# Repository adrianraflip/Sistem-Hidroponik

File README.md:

# Sistem-Hidroponik
Project Sistem Hidroponik

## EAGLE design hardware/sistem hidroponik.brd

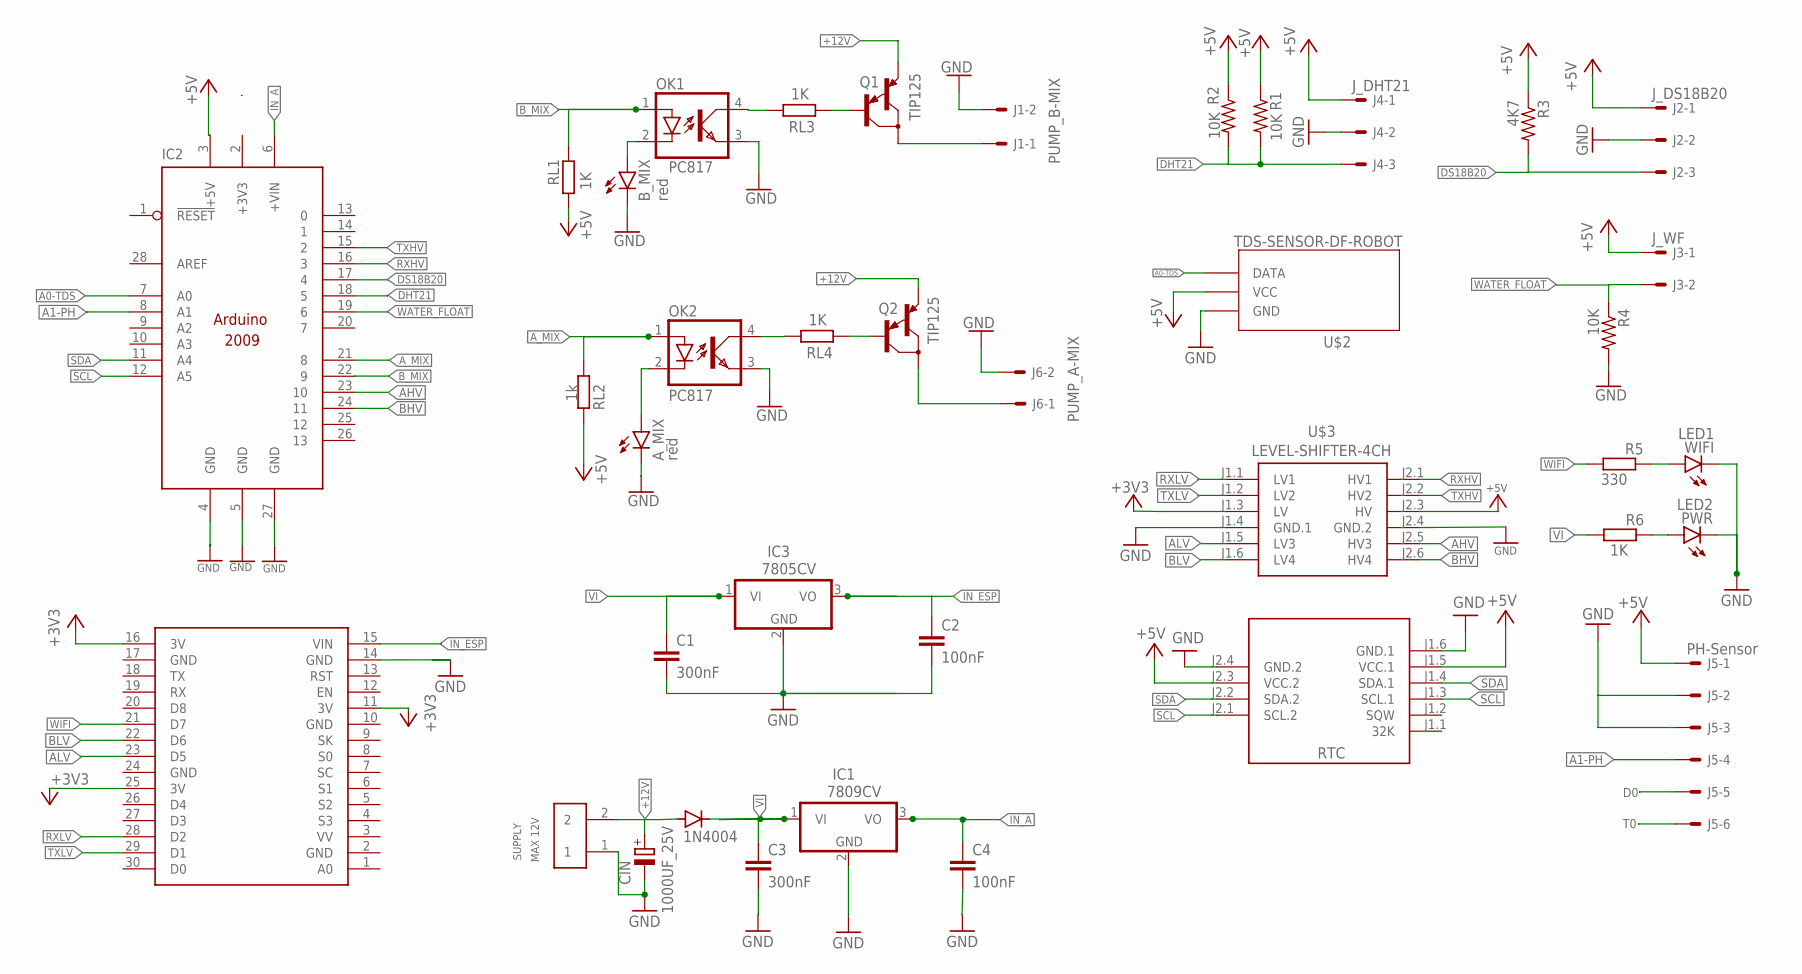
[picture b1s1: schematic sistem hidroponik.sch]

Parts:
1K: R6; 0207/7
330: R5; 0207/7
A_MIX: red; LED3MM
B_MIX: red; LED3MM
C1, C3: 300nF; C025-030X050
C2, C4: 100nF; C025-030X050
CIN: 1000UF_25V; E3,5-8
D1: 1N4004; DO41-10
IC1: 7809CV; TO220H
IC2: ARDUINO2009_10; ARDUINO2009
IC3: 7805CV; TO220H
J1: PUMP_B-MIX; 6410-02
J2: J_DS18B20; 6410-03
J3: J_WF; 6410-02
J4: J_DHT21; 6410-03
J5: PH-Sensor; 6410-06
J6: PUMP_A-MIX; 6410-02
OK1, OK2: PC817; DIL04
PWR: LED2; LED3MM
Q1, Q2: TIP125; TO220
R1, R2, R4: 10K; 0204/7
R3: 4K7; 0204/7
RL1, RL3, RL4: 1K; 0207/7
RL2: 1k; 0207/7
RTC: RTC-DS3231-AT24C32
SUPPLY: MAX 12V; OST_TBLOCK-2PIN
U$1: NODEMCU
U$2: TDS-SENSOR-DF-ROBOT; TDS-SENSOR
U$3: LEVEL-SHIFTER-4CH
WIFI: LED1; LED3MM

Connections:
+3V3: IC2.2 (+3V3), U$1.11 (3V), U$1.16 (3V), U$1.25 (3V), U$3.J1.3 (LV)
+5V: IC2.3 (+5V), J2.1, J3.1, J4.1, J5.1, R1.1, R2.1, R3.1, RL1.1, RL2.2, RTC.J1.5 (VCC.1), RTC.J2.3 (VCC.2), U$2.VCC, U$3.J2.3 (HV)
+12V: CIN.+, D1.A, Q1.3 (E), Q2.3 (E), SUPPLY.2
A0-TDS: IC2.7 (A0), U$2.A (DATA)
A1-PH: IC2.8 (A1), J5.4
AHV: IC2.23 (10), U$3.J2.5 (HV3)
ALV: U$1.23 (D5), U$3.J1.5 (LV3)
A_MIX: IC2.21 (8), OK2.1 (A), RL2.1
BHV: IC2.24 (11), U$3.J2.6 (HV4)
BLV: U$1.22 (D6), U$3.J1.6 (LV4)
B_MIX: IC2.22 (9), OK1.1 (A), RL1.2
D0: J5.5
DHT21: IC2.18 (5), J4.3, R1.2, R2.2
DS18B20: IC2.17 (4), J2.3, R3.2
GND: A_MIX.K (C), B_MIX.K (C), C1.2, C2.2, C3.2, C4.2, CIN.-, IC1.2 (GND), IC2.4 (GND), IC2.5 (GND), IC2.27 (GND), IC3.2 (GND), J1.2, J2.2, J4.2, J5.2, J5.3, J6.2, OK1.3 (EMIT), OK2.3 (EMIT), PWR.K (C), R4.2, RTC.J1.6 (GND.1), RTC.J2.4 (GND.2), SUPPLY.1, U$1.2 (GND), U$1.10 (GND), U$1.14 (GND), U$1.17 (GND), U$1.24 (GND), U$2.GND, U$3.J1.4 (GND.1), U$3.J2.4 (GND.2), WIFI.K (C)
IN_A: C4.1, IC1.3 (VO), IC2.6 (+VIN)
IN_ESP: C2.1, IC3.3 (VO), U$1.15 (VIN)
unnamed: J1.1, Q1.2 (C)
unnamed: 330.1, WIFI.A
unnamed: J6.1, Q2.2 (C)
unnamed: 1K.1, PWR.A
unnamed: B_MIX.A, OK1.2 (C)
unnamed: A_MIX.A, OK2.2 (C)
unnamed: OK2.4 (COL), RL4.2
unnamed: Q2.1 (B), RL4.1
unnamed: Q1.1 (B), RL3.1
unnamed: OK1.4 (COL), RL3.2
RXHV: IC2.16 (3), U$3.J2.1 (HV1)
RXLV: U$1.28 (D2), U$3.J1.1 (LV1)
SCL: IC2.12 (A5), RTC.J1.3 (SCL.1), RTC.J2.1 (SCL.2)
SDA: IC2.11 (A4), RTC.J1.4 (SDA.1), RTC.J2.2 (SDA.2)
T0: J5.6
TXHV: IC2.15 (2), U$3.J2.2 (HV2)
TXLV: U$1.29 (D1), U$3.J1.2 (LV2)
VI: 1K.2, C1.1, C3.1, D1.C, IC1.1 (VI), IC3.1 (VI)
WATER_FLOAT: IC2.19 (6), J3.2, R4.1
WIFI: 330.2, U$1.21 (D7)

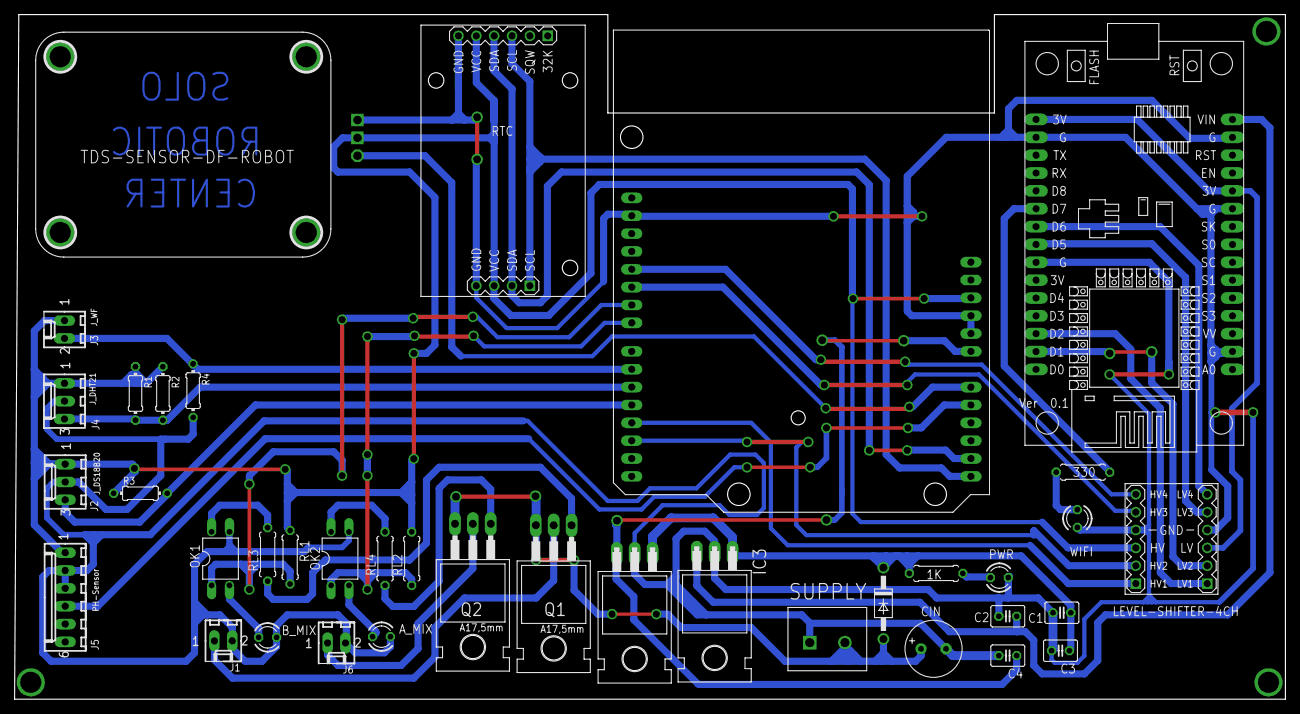
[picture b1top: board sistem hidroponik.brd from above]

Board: 2 copper layers, 180.8 x 97.4 mm, 38 parts (1 on the bottom side), 35 nets.

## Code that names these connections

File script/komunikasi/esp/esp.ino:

/*
ARDUINO UNO 
------------------------
MOTOR A MIX = 8  => LED 
MOTOR B MIX = 9  => LED
WATER FLOAT = 6
DHT 21 = 5
DS18b20 = 4 
TX = 3
TX = 2
AHV = 10
BHV = 11
A0 = TDS SENSOR
A1 = PH SENSOR
A4 = SDA
A5 = SCL 

-----------------------------
ESP8266 
-------------------------------
LED WIFI = D7 GPIO13
BLV = D6
ALV = D5
RXLV = D2 / 4
TXLV = D1 /5
---------------------------------------
led power (1  MERAH)
led wifi (1 hijau)
led ab mix ( 2 kuning )
----------------------------------
D8/gpio15
D4/gpio2
D3/ gpio0
D0/ gpio16
d5 / 14
d6/12
d7/13

---------------------------------------------
ALTERNATIF  PROGRAM KOMUNIKASI BERHASIL
--------------------------------------------
UNO | ESP
2       |  RX
3       | TX

*/


#include <SoftwareSerial.h>
#include <BlynkSimpleEsp8266.h>
#include <ESP8266WiFi.h>
#define BLYNK_PRINT Serial
BlynkTimer timer;
SoftwareSerial remot(4, 5); // RX, TX (GPIO1 , GPIO3)

char auth[] = "xG15115-fjT-1rpi9-wMLvLyCOsrmbO5"; // PASTE YOUR AUTHENTICATION CODE HERE
char ssid[] = "www.tunasfarm.id"; //WIFI NAME
char pass[] = "Tunas@123987-"; //PASSWORD
int i ;
String dataIn;
String dt[50];
boolean parsing = false;

void setup() {
  // put your setup code here, to run once:
  Serial.begin (115200);
  remot.begin(9600);
  Blynk.begin(auth, ssid, pass);
  timer.setInterval(1000L, parsingData);
}


void loop() {
  Blynk.run();
  timer.run();
  if (remot.available() > 0)
  {
    char inChar = (char)remot.read();
    dataIn += inChar;
    if (inChar == '\n') {
      parsing = true;
    }

  }
  if (parsing)
  {
    parsingData();
    parsing = false;
    dataIn = "";
  }
}

void parsingData()
{
  int j = 0;
  //kirim data yang telah diterima sebelumnya

  //inisialisasi variabel, (reset isi variabel)
  dt[j] = "";
  //Serial.print(dataIn);
  //proses parsing data
  for (i = 1; i < dataIn.length(); i++)
  {
    //pengecekan tiap karakter dengan karakter (#) dan (,)
    if ((dataIn[i] == '&') || (dataIn[i] == ','))
    {
      //increment variabel j, digunakan untuk merubah index array penampung
      j++;
      dt[j] = ""; //inisialisasi variabel array dt[j]
    }
    else
    {
      //proses tampung data saat pengecekan karakter selesai.
      dt[j] = dt[j] + dataIn[i];
    }

  }
  //Serial.println (dt[0]) ;
  //Serial.println (dt[1]) ;
  //Serial.print (dt[2]) ;
  //delay(30000);
  //Serial.println("************");
  String data1 = "&" + dt[0] + "," + dt[1] + "," + dt[2] + dt[3] + "," + dt[4] + "," + dt[5];
  Serial.print("KIRIM DATA: ");
  //client.print(dt[0]); // kirim data
  //client.print(dt[1]);
  //client.print(dt[2]);
  Serial.print(data1);
  Blynk.virtualWrite(V1, dt[0]);
  Blynk.virtualWrite(V2, dt[1]);
  Blynk.virtualWrite(V3, dt[2]);
  Blynk.virtualWrite(V4, dt[3]);

}

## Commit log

2021-04-12 First Upload
2021-04-12 Second Upload
2021-04-12 Third Upload

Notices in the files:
parts and their libraries:
diy-modules: Released under the Creative Commons Attribution 4.0 International License: http://creativecommons.org/licenses/by/4.0
